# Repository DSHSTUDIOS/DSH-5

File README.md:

# DSH-5

I wanted a DJ deck I could hold in one hand. The DSH-5 has a motorized platter for scratching, a small OLED, one crossfader and one level knob. REC, MIX and PLAY are on the right edge. The seesaw on the left speeds up or slows down the track.

## Playing it

1. Put a stereo, 16-bit, 44.1 kHz `BACKING.WAV` on a microSD card. The deck loops the first 30 seconds. Add a `SCRATCH.WAV` for a separate sample. The wheel uses the backing track if there is no sample or recording.
2. Hold **PLAY** to turn it on. Tap **PLAY** to start or pause. Press either end of the seesaw to change the backing track speed.
3. Tap **MIX** to scratch. The motor lets the platter coast, and turning it moves the scratch sample. Use the crossfader to blend it with the backing track. The knob sets the output level.
4. Tap **REC** to capture up to eight seconds from line in. Tap it again to save the take and use it as the scratch sample.

## Design screenshots

### Enclosure and board

### Rev E PCB

## Rev E prototype

Rev E uses a solder-down ESP32-S3, a bare OLED, and an onboard stereo codec. The main board carries the crossfader, level pot, three side buttons and the two speed-seesaw contacts.

| What | Where |
| --- | --- |
| PCB | [KiCad project](hardware/rev-e/kicad/DSH-5-PCB-RevE.kicad_pro) · [board](hardware/rev-e/kicad/DSH-5-PCB-RevE.kicad_pcb) · [schematic](hardware/rev-e/kicad/DSH-5-PCB-RevE.kicad_sch) |
| Parts and sourcing | [Full BOM](BOM.csv) · [Fallen BOM](FALLEN-BOM.csv) |
| Mechanical reference | [Populated PCB STEP](cad/DSH-5-RevE-PCB.step.xz) |
| Wiring and assembly | [Hardware and turnkey assembly notes](hardware/rev-e/README.md) · [KiCad and firmware reports](hardware/rev-e/checks/) |
| Firmware | [ESP32-S3 source](firmware/rev-e/src/) · [PlatformIO project](platformio.ini) |

Run `pio run` from the repository root to build Rev E. Unpack the PCB model with `xz -dk cad/DSH-5-RevE-PCB.step.xz` and open the resulting STEP in Fusion.

KiCad reports zero errors and zero open connections, with two warnings documented in the hardware notes. The firmware builds. Physical fit, charging, audio and the motor still need first-article testing.

## Rev D files

The studio render and enclosure images above show Rev D. Its [enclosure and fit notes](cad/README.md), [KiCad source](hardware/kicad/DSH-5-PCB-RevD.kicad_pro), [turnkey quote files](hardware/manufacturing/pcba/), and [Teensy firmware](firmware/README.md) are available for that revision. The [Rev D BOM](https://github.com/DSHSTUDIOS/DSH-5/blob/5f626b1eb498d4edce1bb6fbd1a963682ae008fc/BOM.csv) is in the prior release commit.

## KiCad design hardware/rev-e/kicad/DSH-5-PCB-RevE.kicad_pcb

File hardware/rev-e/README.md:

# DSH-5 Rev E

Rev E puts the microcontroller, audio codec, display support, microSD and 3.3 V supply on the DSH-5 main board. The four-layer, 80 × 176 mm board carries the 30 mm crossfader, level potentiometer, three side switches and two switches for the opposite-side seesaw.

## Hardware

| Reference | Implementation |
| --- | --- |
| U1 | Solder-down ESP32-S3-WROOM-1-N16R8 with 16 MB flash and 8 MB PSRAM. |
| DS1 and J20 | Bare 0.96-inch Winstar OLED with 30-pin FPC and 0.5 mm ZIF connector. The main PCB provides the SSD1306 charge-pump capacitors and current reference. The I²C address is 0x3C. |
| J6 and U2 | JST-XH alternate line input. The main PCB provides ESD protection, 1 kΩ series protection, 100 kΩ bias returns and 2.2 µF AC coupling into the TLV320AIC3204 codec. J11 is the alternative 3.5 mm input. Connect one source at a time. |
| J12 and J13 | Separate 3.5 mm line and headphone outputs from the onboard codec. |
| J21 | Direct-mounted microSD socket on SPI with its own chip select. |
| U14 and U3 | Onboard MCP2518FD CAN-FD controller and TCAN3413 PHY. This preserves the interface to the motor controller. |
| J1 and J2 | USB-C PD charging and internal protected 3S battery. The USB-C connector supplies power. J19 provides the firmware service interface. |

The GL30 motor, moteus-c1 controller and Pololu 12 V regulator remain chassis-mounted. The full BOM includes them. The Fallen CSV excludes the two ready-made chassis boards from the funding request. Every row has a USD price and a sourcing link. Listed prices and estimates are identified in the full BOM. The OLED price is a per-deck budget figure based on an 11-piece supplier minimum. The custom battery and harnesses have budget figures pending quotes. The full budget is $602.63 and the Fallen budget is $503.68, including a $250.00 CNC enclosure allowance. These subtotals precede supplier order minimums, PCB and harness assembly labor, tax and shipping.

## Files

- `kicad/DSH-5-PCB-RevE.kicad_pro` opens the editable schematic and PCB. KiCad 10 standard footprint and 3D model libraries supplement the local project libraries.
- [DSH-5-RevE-PCB.step.xz](../../cad/DSH-5-RevE-PCB.step.xz) contains the populated PCB reference for Fusion. Run `xz -dk cad/DSH-5-RevE-PCB.step.xz` from the repository root to extract it. Its origin is the board's upper-left corner. The OLED panel and motor mount separately in the enclosure. Fit a nonconductive fastener at H2 and keep metal out of the antenna area. Recheck the OLED flex fold, microSD access, service header and headphone cutout with physical samples.
- [BOM.csv](../../BOM.csv) lists components and sourcing links. [FALLEN-BOM.csv](../../FALLEN-BOM.csv) uses the proposal's CSV columns.
- Build the [ESP32-S3 firmware](../../firmware/rev-e/src/) with `pio run` from the repository root. The PlatformIO board manifest configures the compiler and flash settings.

## Verification

The schematic passed KiCad electrical checks. The PCB passed routing and schematic parity checks with zero errors and no unconnected items. KiCad flags the customized ESP32 antenna footprint because its placement rule allows the nearby unplated H2 mounting hole. The area still excludes pads, tracks, vias and copper pours. KiCad also reports an unterminated copper branch with continuity intact. The ESP32-S3 firmware compiled. Physical OLED fit, USB-C charging, audio and motor behavior still need first-article validation.

## CNC enclosure

Budget one CNC-machined chassis, front plate and rear cover. The allowance assumes 6061 aluminum with a standard machined finish. The enclosure STEP in the repository is from Rev D. Check the Rev E OLED, microSD, headphones, service access and antenna clearance in the enclosure before quoting the final case.

The battery tray budget is 65 × 37 × 20 mm. The pack vendor needs to confirm the complete wrapped dimensions, wire exit and connector fit as well as cell balancing, 12.6 V charge termination, 1 A charge and at least 3 A continuous discharge. The BT1 link is for sourcing a custom configuration. [PCBWay CNC quote](https://www.pcbway.com/rapid-prototyping/)

## Turnkey assembly

Quote both-sided SMT, through-hole controls and connectors, and factory programming. Specify that the assembled board should arrive with all soldering finished. If the order includes the whole deck, quote installing the OLED into J20, mounting the controls and motor stack, and building the keyed chassis harnesses as separate integration operations.

J19 pin order is GND, ESP TX, ESP RX, BOOT, EN, and 3.3 V reference. Use a 3.3 V UART fixture. For download mode, hold BOOT low while cycling EN low then high. Use `pio run -t upload` through the fixture after the board is powered. The USB-C connector is for charging.

[Winstar OLED panel options](https://www.winstar.com.tw/products/oled-module/graphic-oled-display/0_96-oled.html) · [ESP32-S3 module datasheet](https://documentation.espressif.com/esp32-s3-wroom-1_wroom-1u_datasheet_en.pdf) · [TI audio codec](https://www.ti.com/product/TLV320AIC3204) · [PCBWay turnkey assembly quote](https://www.pcbway.com/quotesmt.aspx)

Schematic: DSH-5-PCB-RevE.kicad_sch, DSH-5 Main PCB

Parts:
C1: 470u / 35V; CP_Radial_D10.0mm_P5.00mm
C2, C24, C25, C26, C42, C55: 100n / 50V; C_0603_1608Metric
C3, C4, C5, C6: 100n; C_0805_2012Metric
C10, C11: 330p; C_0603_1608Metric
C12: 1n; C_0603_1608Metric
C13, C14, C51, C61, C74, C75, C94: 10u / 10V; C_0805_2012Metric
C15, C22: 4.7u / 10V; C_0805_2012Metric
C16: 4.7u / 35V; C_0805_2012Metric
C17: 10n / 50V; C_0603_1608Metric
C18, C19: 22u / 35V; C_1206_3216Metric
C20, C21: 47n / 25V; C_0603_1608Metric
C23: 1n / 50V; C_0402_1005Metric
C27, C28, C29, C30, C31, C32, C33, C34, C35, C36, C37, C38, C53: 10u / 35V; C_1206_3216Metric
C43, C46, C52, C58, C59, C60, C85, C92, C95: 100n; C_0603_1608Metric
C44: 330n; C_0603_1608Metric
C50, C56, C57, C62, C84, C93: 1u / 10V; C_0805_2012Metric
C54: 22u / 10V; C_1206_3216Metric
C70, C71: 2.2u / 10V; C_0805_2012Metric
C76, C77: 47u / 10V; C_1206_3216Metric
C80, C81: 1u / 16V; C_0805_2012Metric
C82, C83: 1u / 25V; C_0805_2012Metric
C90, C91: 15p C0G; C_0603_1608Metric
D1, D10: SMBJ16A; D_SMB
D4: SS54; D_SMC
D5: BZT52C10; D_SOD-123
D6, D7, D8, D9, D11, D12: PESD5V0S1BA; D_SOD-323
F1: 2 A / 32 V; Fuse_1206_3216Metric
F2: 3 A / 32 V; Fuse_1206_3216Metric
J1: USB-C CHARGE; USB_C_Receptacle_GCT_USB4125-xx-x_6P_TopMnt_Horizontal
J2: BATTERY; Battery_VH_2Pin_Edge
J3: PACK TEMP; JST_PH_B2B-PH-K_1x02_P2.00mm_Vertical
J4: BRAKE RESISTOR; JST_VH_B2P-VH_1x02_P3.96mm_Vertical
J6: AUX STEREO LINE IN; JST_XH_B3B-XH-A_1x03_P2.50mm_Vertical
J7: STEREO LINE OUT HEADER; JST_XH_B3B-XH-A_1x03_P2.50mm_Vertical
J8: CHARGER DEBUG; JST_XH_B3B-XH-A_1x03_P2.50mm_Vertical
J11: STEREO LINE IN; Line_Jack_SJ3523SMT
J12: STEREO LINE OUT; Line_Jack_SJ3523SMT
J13: HEADPHONES; Line_Jack_SJ3523SMT
J17: MOTEUS CAN; JST_PH_B3B-PH-K_1x03_P2.00mm_Vertical
J18: MOTEUS POWER; JST_VH_B2P-VH_1x02_P3.96mm_Vertical
J19: 3V3 UART SERVICE; PinHeader_1x06_P2.54mm_Vertical
J20: OLED FPC; Hirose_FH12-30S-0.5SH_1x30-1MP_P0.50mm_Horizontal
J21: MICROSD SPI; microSD_HC_Hirose_DM3AT-SF-PEJM5
L1: 2.2uH; L_Coilcraft_XAL6060-XXX
L2: 2.2uH; L_Wuerth_MAPI-3012
Q1: IRLML6344; SOT-23
Q2: DMP3010LK3; TO-252-3_TabPin2
Q3: 2N7002; SOT-23
R1: 120R; R_0805_2012Metric
R3, R4: 1k; R_0805_2012Metric
R5: 10k; R_0805_2012Metric
R10: 82.5k 1%; R_0603_1608Metric
R11, R13, R31: 10k 1%; R_0603_1608Metric
R12: 200k 1%; R_0603_1608Metric
R14: 69.8k 1%; R_0603_1608Metric
R15, R23: 30.1k 1%; R_0603_1608Metric
R16, R21, R47: 100k 1%; R_0603_1608Metric
R17: 13k 1%; R_0603_1608Metric
R18: 0R; R_0603_1608Metric
R19: 13.7k 1%; R_0603_1608Metric
R20: 162k 1%; R_0603_1608Metric
R22: 5.23k 1%; R_0603_1608Metric
R24, R42, R43, R44, R45: 100R; R_0603_1608Metric
R25, R26, R27, R40, R41, R50, R51, R55, R70, R71, R72, R73, R74, R75, R76: 10k; R_0603_1608Metric
R30: 49.9k 1%; R_0603_1608Metric
R32: 1M 1%; R_0603_1608Metric
R33, R34: 2.2k; R_0603_1608Metric
R46, R58, R59, R62, R63: 100k; R_0603_1608Metric
R48: 24.9k 1%; R_0603_1608Metric
R53, R54: 4.7k; R_0603_1608Metric
R56, R57: 1k; R_0603_1608Metric
R60, R61: 47k; R_0603_1608Metric
R66: 910k; R_0603_1608Metric
RV1: B10k fader; Potentiometer_Bourns_PTA3043_Single_Slide
RV2: B10k knob; Potentiometer_Bourns_PTV09A-1_Single_Vertical
SW1: REC; SW_Tactile_SPST_Angled_PTS645Vx39-2LFS
SW2: MIX; SW_Tactile_SPST_Angled_PTS645Vx39-2LFS
SW3: PLAY / POWER; SW_Tactile_SPST_Angled_PTS645Vx39-2LFS
SW4: SPEED +; SW_Tactile_SPST_Angled_PTS645Vx39-2LFS
SW5: SPEED -; SW_Tactile_SPST_Angled_PTS645Vx39-2LFS
U1: ESP32-S3-WROOM-1-N16R8; ESP32-S3-WROOM-1
U2: TLV320AIC3204; Texas_RHB0032E_VQFN-32-1EP_5x5mm_P0.5mm_EP3.45x3.45mm
U3: TCAN3413DR; SOIC-8_3.9x4.9mm_P1.27mm
U4: TPS62162; Texas_DSG0008A_WSON-8-1EP_2x2mm_P0.5mm_EP0.9x1.6mm
U6: MOTOR REGULATOR HARNESS; JST_VH_B4P-VH_1x04_P3.96mm_Vertical
U7: TPS25730D; Texas_REF0038A_WQFN-38-2EP_6x4mm_P0.4
U8: TPS22810; SOT-23-6
U9: BQ25798; Texas_RQM0029A_VQFN-29_4x4mm_P0.4mm
U10: LTC2954-1; TSOT-23-8
U11: TLV1701; SOT-23-5
U12: TL431A; SOT-23
U13: TLV75518; SOT-23-5
U14: MCP2518FD; SOIC-14_3.9x8.7mm_P1.27mm
Y1: 40MHz; Crystal_SMD_3225-4Pin_3.2x2.5mm

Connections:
/+3V3: C3.1, C4.1, C51.1, C52.1, C54.1, C56.1, C58.1, C62.1, C84.1, C85.1, C92.1, C93.1, C94.1, C95.1, J19.6 (VREF), J20.6 (VBAT), J20.9 (VDD), J20.11 (BS1), J21.4 (VDD), L2.2 (3V3), Q3.1 (GATE), R5.1, R25.1, R26.1, R27.1, R40.1, R41.1, R50.1, R51.1, R53.1, R54.1, R70.1, R71.1, R72.1, R73.1, R74.1, R75.1, R76.1, RV1.3 (Low), RV2.3 (Low), U1.2 (3V3), U2.6 (IOVDD), U2.26 (LDOIN), U3.3 (VCC), U3.5 (VIO), U4.6 (VOS), U13.1 (IN), U13.3 (EN), U14.14 (VDD)
/AUX_IN_L: D11.1 (K), J6.1 (L), R56.1
/AUX_IN_R: D12.1 (K), J6.3 (R), R57.1
/BAT_FUSED: C27.1, C28.1, F2.2, Q2.3 (SOURCE), R24.1, R46.1, U9.22 (BAT), U9.23 (BAT)
/BRAKE_GATE: D5.1 (K), Q1.1 (GATE), R32.1, R33.2, U11.4 (OUT)
/BRAKE_REF: R34.2, U11.3 (IN-), U12.1 (REF), U12.2 (CATHODE)
/BRAKE_RETURN: J4.2 (RETURN), Q1.3 (DRAIN)
/BRAKE_SENSE: R30.2, R31.1, R32.2, U11.1 (IN+)
/BST1: C20.1, U9.4 (BTST1)
/BST2: C21.1, U9.19 (BTST2)
/CAN_CS_N: R70.2, U1.34 (IO41), U14.13 (CS#)
/CAN_H: J17.1 (CAN_H), R1.1, U3.7 (CANH)
/CAN_IRQ_N: R71.2, U1.11 (IO18), U14.4 (INT)
/CAN_L: J17.2 (CAN_L), R1.2, U3.6 (CANL)
/CAN_RX: U3.4 (RXD), U14.2 (RXCAN)
/CAN_TX: R5.2, U3.1 (TXD), U14.1 (TXCAN)
/CAN_XI: C90.1, U14.6 (OSC1), Y1.1 (XI)
/CAN_XO: C91.1, U14.5 (OSC2), Y1.3 (XO)
/CHG_DM: R18.2, U9.7 (D-)
/CHG_DP: R18.1, U9.6 (D+)
/CHG_ILIM: R20.2, R21.1, U9.17 (ILIM_HIZ)
/CHG_N: R25.2, U1.24 (IO47), U9.1 (STAT)
/CHG_PMID: C25.1, C31.1, C32.1, C33.1, U9.29 (PMID)
/CHG_PROG: R19.1, U9.20 (PROG)
/CHG_REGN: C22.1, R20.1, R22.1, U9.5 (REGN)
/CHG_SCL: J8.2 (SCL), R26.2, U9.14 (SCL)
/CHG_SDA: J8.1 (SDA), R27.2, U9.15 (SDA)
/CHG_SDRV: C23.1, U9.24 (SDRV)
/CHG_SENSE: R24.2, U9.18 (BATP)
/CHG_SW1: C20.2, L1.1 (SW1), U9.28 (SW1)
/CHG_SW2: C21.2, L1.2 (SW2), U9.26 (SW2)
/CHG_VIN: C24.1, C29.1, C30.1, U8.6 (VOUT), U9.2 (VBUS), U9.3 (VBUS), U9.8 (VAC2), U9.9 (VAC1)
/CODEC_1V8: C57.1, C59.1, C60.1, U2.24 (AVDD), U2.29 (DVDD), U13.5 (OUT)
/CODEC_HPL: C76.1, U2.25 (HPL)
/CODEC_HPR: C77.1, U2.27 (HPR)
/CODEC_IN_L: C70.2, U2.13 (IN1_L)
/CODEC_IN_R: C71.2, U2.14 (IN1_R)
/CODEC_LOL: C74.1, U2.22 (LOL)
/CODEC_LOR: C75.1, U2.23 (LOR)
/CODEC_REF: C61.1, U2.18 (REF)
/CODEC_RESET: R55.1, U1.23 (IO21), U2.31 (RESET)
/GND: C1.2 (-), C2.2, C3.2, C4.2, C5.2, C6.2, C10.2, C11.2, C12.2, C13.2, C14.2, C15.2, C16.2, C17.2, C18.2, C19.2, C22.2, C23.2, C24.2, C25.2, C26.2, C27.2, C28.2, C29.2, C30.2, C31.2, C32.2, C33.2, C34.2, C35.2, C36.2, C37.2, C38.2, C42.2, C43.2, C44.2, C46.2, C50.2, C51.2, C52.2, C53.2, C54.2, C55.2, C56.2, C57.2, C58.2, C59.2, C60.2, C61.2, C62.2, C82.2, C83.2, C84.2, C85.2, C90.2, C91.2, C92.2, C93.2, C94.2, C95.2, D1.2 (A), D5.2 (A), D6.2 (A), D7.2 (A), D8.2 (A), D9.2 (A), D10.2 (A), D11.2 (A), D12.2 (A), J1.A12 (GND), J1.B12 (GND), J1.SH (SHELL), J2.2 (PACK_-), J3.2 (GND), J6.2 (GND), J7.2 (GND), J8.3 (GND), J11.S (GND), J12.S (GND), J13.S (GND), J17.3 (GND), J18.2 (GND), J19.1 (GND), J20.1 (NC_GND), J20.8 (VSS), J20.10 (BS0), J20.12 (BS2), J20.13 (CS#), J20.15 (SA0), J20.16 (R/W#), J20.17 (E/RD#), J20.21 (D3), J20.22 (D4), J20.23 (D5), J20.24 (D6), J20.25 (D7), J20.29 (VLSS), J20.30 (NC_GND), J21.6 (VSS), J21.SH (SHIELD), Q1.2 (SOURCE), Q3.2 (SOURCE), R11.2, R13.2, R15.2, R17.2, R19.2, R21.2, R23.2, R31.2, R48.2, R55.2, R58.2, R59.2, R60.2, R61.2, R62.2, R63.2, R66.2, RV1.1 (High), RV2.1 (High), SW1.2 (COM), SW2.2 (COM), SW3.2 (COM), SW4.2 (COM), SW5.2 (COM), U1.1 (GND), U1.40 (GND), U1.41 (EPAD), U2.7 (IOVSS), U2.8 (SCLK), U2.12 (SPI_SELECT), U2.17 (AVSS), U2.28 (DVSS), U2.30 (LDO_SELECT), U2.33 (EP), U3.2 (GND), U3.8 (STB), U4.1 (PGND), U4.4 (AGND), U4.5 (FB), U4.9 (EP), U6.3 (GND), U7.8 (I2C_SDA), U7.9 (I2C_SCL), U7.11 (PGND), U7.12 (PGND), U7.14 (PGND), U7.16 (PGND), U7.17 (PGND), U7.26 (RESERVED), U7.27 (RESERVED), U7.31 (PGND), U7.34 (PGND), U7.36 (RESERVED), U7.39 (PGND), U8.2 (GND), U9.10 (ACDRV2), U9.11 (ACDRV1), U9.13 (CE), U9.27 (GND), U10.4 (GND), U11.2 (V-), U12.3 (ANODE), U13.2 (GND), U14.7 (VSS), Y1.2 (CASE), Y1.4 (CASE)
/HP_L: C76.2, J13.T (L), R62.1
/HP_R: C77.2, J13.R, R63.1
/I2C_SCL: J20.18 (D0_SCL), R53.2, U1.19 (IO11), U2.9 (SCL)
/I2C_SDA: J20.19 (D1_SDA), J20.20 (D2_SDA), R54.2, U1.18 (IO10), U2.10 (SDA)
/I2S_ADC: U1.9 (IO16), U2.5 (DOUT)
/I2S_BCLK: U1.21 (IO13), U2.2 (BCLK)
/I2S_DAC: U1.8 (IO15), U2.4 (DIN)
/I2S_LRCLK: U1.22 (IO14), U2.3 (WCLK)
/I2S_MCLK: U1.20 (IO12), U2.1 (MCLK)
/KILL_OK: R41.2, U10.8 (KILL)
/LEVEL_ADC: C6.1, R4.2, U1.38 (IO2)
/LINE_IN_L: C70.1, R42.2, R56.2, R58.1
/LINE_IN_L_EXT: D6.1 (K), J11.T (LEFT), R42.1
/LINE_IN_R: C71.1, R43.2, R57.2, R59.1
/LINE_IN_R_EXT: D7.1 (K), J11.R (RIGHT), R43.1
/LINE_OUT_L: C74.2, J7.1 (L), R44.2, R60.1
/LINE_OUT_L_EXT: D8.1 (K), J12.T (LEFT), R44.1
/LINE_OUT_R: C75.2, J7.3 (R), R45.2, R61.1
/LINE_OUT_R_EXT: D9.1 (K), J12.R (RIGHT), R45.1
/LOGIC_SW: L2.1 (SW), U4.7 (SW)
/MCU_BOOT_N: J19.4 (BOOT), R51.2, U1.27 (IO0)
/MCU_EN: C50.1, J19.5 (EN), R50.2, U1.3 (EN)
/MIX_N: SW2.1 (NO), U1.6 (IO6)
/MOTOR_FUSED: D4.2 (A), F1.2
/MOTOR_RAW: F1.1, U6.4 (VOUT)
/OLED_C1N: C80.2, J20.5 (C1N)
/OLED_C1P: C80.1, J20.4 (C1P)
/OLED_C2N: C81.2, J20.2 (C2N)
/OLED_C2P: C81.1, J20.3 (C2P)
/OLED_COM: C83.1, J20.27 (VCOMH)
/OLED_IREF: J20.26 (IREF), R66.1
/OLED_PANEL_VCC: C82.1, J20.28 (VCC)
/OLED_RESET: J20.14 (RES#), U1.10 (IO17)
/PACK_RAW: F2.1, J2.1 (PACK_+)
/PACK_TS: J3.1 (NTC), R22.2, R23.1, U9.16 (TS)
/PD_1V5: C15.1, U7.3 (ADCIN2), U7.4 (LDO_1V5)
/PD_3V3: C14.1, R10.1, R12.1, R14.1, U7.1 (LDO_3V3), U7.18 (FAULT_IN)
/PD_DRAIN: U7.15 (DRAIN), U7.30 (DRAIN), U7.40 (DRAIN_PAD)
/PD_IMAX: R14.2, R15.1, U7.7 (ADCIN4)
/PD_IOP: R12.2, R13.1, U7.5 (ADCIN3)
/PD_MIN: R10.2, R11.1, U7.2 (ADCIN1)
/PD_SLEW: C12.1, U8.4 (CT)
/PD_VIN_3V3: C13.1, U7.38 (VIN_3V3)
/PD_VOUT: C18.1, C19.1, R16.1, U7.20 (PPHV), U8.1 (VIN)
/PD_VQUAL: R16.2, R17.1, U8.3 (EN)
/PLAY_N: R40.2, U1.7 (IO7), U10.5 (INT)
/POWER_BUTTON_N: SW3.1 (NO), U10.2 (PB)
/POWER_EN: U4.3 (EN), U6.1 (EN), U10.6 (EN)
/REC_N: SW1.1 (NO), U1.5 (IO5)
/SD_CS_N: J21.2 (DAT3_CS), R72.2, U1.35 (IO42)
/SD_DAT1: J21.8 (DAT1), R73.2
/SD_DAT2: J21.1 (DAT2), R74.2
/SENSE_GATE: Q2.1 (GATE), Q3.3 (DRAIN), R46.2
/SENSE_SRC: Q2.2 (DRAIN), R47.1
/SPEED_DN_N: SW5.1 (NO), U1.17 (IO9)
/SPEED_UP_N: SW4.1 (NO), U1.12 (IO8)
/SPI_MISO: J21.7 (DAT0), R76.2, U1.33 (IO40), U14.12 (SDO)
/SPI_MOSI: J21.3 (CMD), R75.2, U1.32 (IO39), U14.11 (SDI)
/SPI_SCK: J21.5 (CLK), U1.31 (IO38), U14.10 (SCK)
/SW_ONT: C43.1, U10.3 (ONT)
/SW_PDT: C44.1, U10.7 (PDT)
/SYS_BAT: C26.1, C34.1, C35.1, C36.1, C37.1, C38.1, C53.1, C55.1, U4.2 (VIN), U6.2 (VIN), U9.25 (SYS), U10.1 (VIN)
/UART_RX: J19.3 (ESP_RX), U1.36 (RXD0)
/UART_TX: J19.2 (ESP_TX), U1.37 (TXD0)
/USB_CC1: C10.1, J1.A5 (CC1), U7.28 (CC1)
/USB_CC2: C11.1, J1.B5 (CC2), U7.29 (CC2)
/USB_VBUS: C16.1, C17.1, D10.1 (K), J1.A9 (VBUS), J1.B9 (VBUS), U7.23 (VBUS_IN), U7.32 (LDO_VBUS)
/VBAT_ADC: C46.1, R47.2, R48.1, U1.4 (IO4)
/VM_12V: C1.1 (+), C2.1, C42.1, D1.1 (K), D4.1 (K), J4.1 (VM), J18.1 (VM_+), R30.1, R33.1, R34.1, U11.5 (V+)
/XFADER_ADC: C5.1, R3.2, U1.39 (IO1)
unnamed: R3.1, RV1.2 (Wiper)
unnamed: R4.1, RV2.2 (Wiper)

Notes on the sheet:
Verify pin-1 orientation, exposed contact side and fold in a physical sample.
ONBOARD STEREO CODEC / INPUT AND OUTPUT
RAW SSD1306 OLED / 30-PIN FPC
USB-C POWER DELIVERY / INPUT QUALIFICATION
BQ25798 POWER PATH / PROTECTED 3S BATTERY
FRONT CONTROLS / DIRECT PCB MOUNT
Set codec inputs and common-mode in firmware before enabling audio.
DS1: Winstar WEO012864DWPP3N00F04 bare OLED.
SSD1306 I2C address 0x3C. Use internal charge pump.
The 3.3 V buck powers the logic and raises KILL_OK.
J6 or J11 is the stereo source. Use one at a time.
OLED uses J20 and on-board charge pump passives.
SUPPLY / POWER BUTTON / MONITORING
Place CC filters and raw VBUS decoupling at the PD controller. Do not ground PD_DRAIN.
RV1 is the crossfader. RV2 sets output level.
MOTOR RAIL / REVERSE ISOLATION / REGENERATIVE SHUNT
Use the specified external pulse resistor. Start with conservative moteus current and regen limits.
SCRATCH MOTOR / MOTEUS-C1
J17 is carrier order H/L/GND; match the moteus connector by SIGNAL.
Keep copper and metal away from the antenna area.
Connect a protected, balanced 3S pack rated for 1 A charge and 3 A continuous discharge.
BOARD-MOUNT STEREO AUDIO / BATTERY SENSE
Control power stays off until PLAY is held. Brief presses drive the ESP32.
SW1-SW3 mount at the right edge. SW4 and SW5 sit under one left-edge rocker.
GPIO35–37 are reserved by octal PSRAM. Flash through J19.
The rocker returns to center. SW3 goes to the power controller. ESP32 reads the controller INT output.
Autonomous charge configuration: 3S, 12.60 V, 1.00 A, 750 kHz. Charge can run while the deck is off.
Shunt turns on near 15 V and off near 14.5 V.
Input bleed and ESD are on board. AC couple into internally biased PGA.
DSH-5 / PCB REV E
ESP32-S3 / CONTROLS / SERVICE
GL30 motor phases U/V/W wire directly to moteus, outside this PCB.
CAN-FD CONTROLLER / MICROSD
Current limited to about 1.15 A at the charger input. Requires a 12 V or 15 V USB-PD source.
Fit a second 120R terminator at the far controller end.
FOUR-LAYER MAIN BOARD | FRONT WHEEL + FADER + KNOB | SIDE REC / MIX / PLAY
See assembly STEP for the GL30 platter stack and magnetic encoder gap.
The local D+/D- strap selects DCP limits after the PD switch. The analog input ceiling is lower.
ONBOARD 3.3 V LOGIC SUPPLY
Separate SPI chip selects. Configure 1 Mbps arbitration and 5 Mbps data, verify against motor setup.

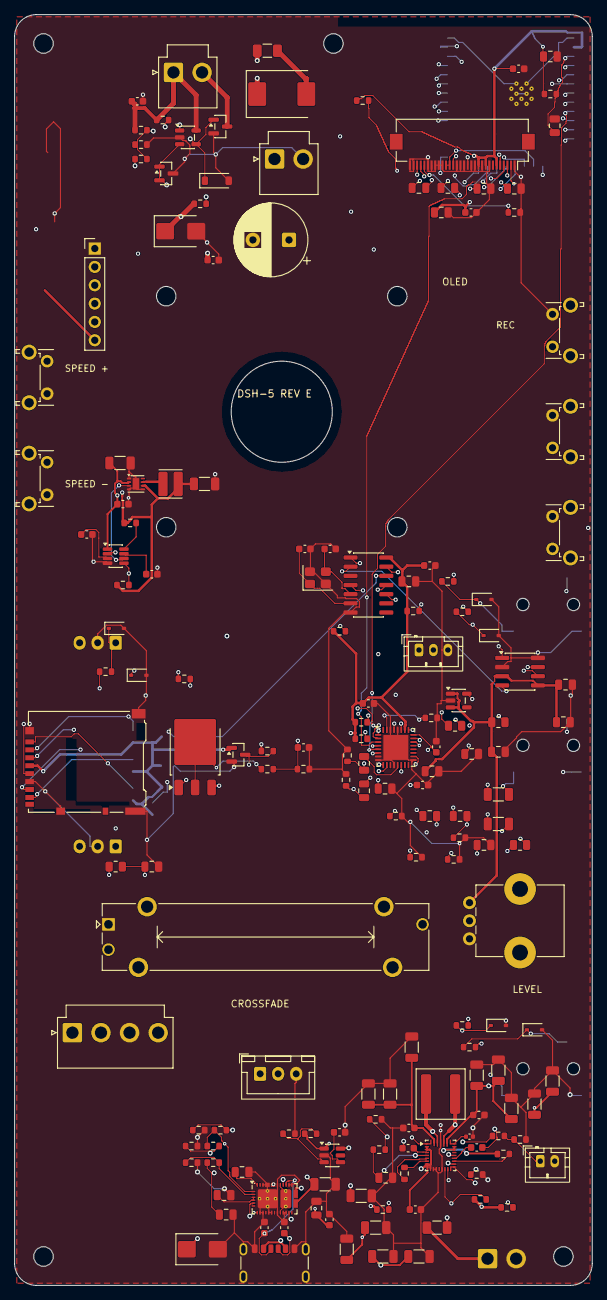
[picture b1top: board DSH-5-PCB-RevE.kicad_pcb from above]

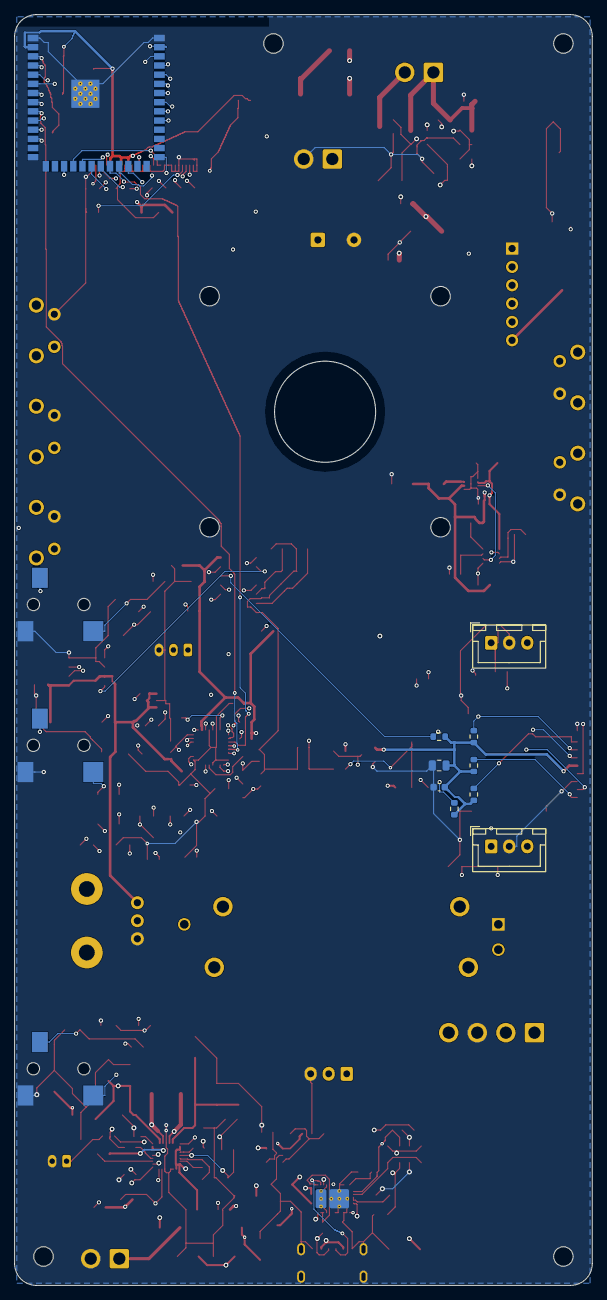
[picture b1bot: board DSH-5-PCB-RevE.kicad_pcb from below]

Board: 4 copper layers, 80.0 x 176.0 mm, 188 parts (13 on the bottom side), 114 nets.

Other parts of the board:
H1, H2, H3, H4, H5, H6, H7, H8: M2.5; MountingHole_2.7mm_M2.5

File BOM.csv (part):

Designator,Quantity,Part or value,Footprint,Assembly role,Assembly scope,Quote part or specification,Unit price USD,Extended price USD,Price type,Price source,Price checked,Procurement notes
C1,1,Panasonic EEU-FR1V471,Capacitor_THT:CP_Radial_D10.0mm_P5.00mm,,Main PCB,Panasonic EEU-FR1V471,1.08,1.08,Listed,https://www.digikey.com/en/products/detail/panasonic-industr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,2026-11-22,Polarity and body clearance.
C10,1,330p,Capacitor_SMD:C_0603_1608Metric,,Main PCB,330 pF 50 V C0G ±5%,0.12,0.12,Estimate,https://www.digikey.com/en/products/result?keywords=330+pF+5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,2026-11-22,Assembler may source to the listed requirements.
C11,1,330p,Capacitor_SMD:C_0603_1608Metric,,Main PCB,330 pF 50 V C0G ±5%,0.12,0.12,Estimate,https://www.digikey.com/en/products/result?keywords=330+pF+5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,2026-11-22,Assembler may source to the listed requirements.
C12,1,1n,Capacitor_SMD:C_0603_1608Metric,,Main PCB,1 nF 50 V C0G ±5%,0.14,0.14,Estimate,https://www.digikey.com/en/products/result?keywords=1+nF+50+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,2026-11-22,Assembler may source to the listed requirements.
C13,1,10u / 10V,Capacitor_SMD:C_0805_2012Metric,,Main PCB,10 µF ≥10 V X5R/X7R ±20%,0.24,0.24,Estimate,https://www.digikey.com/en/products/result?keywords=10+%C2%B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,2026-11-22,Assembler may source to the listed requirements.
C14,1,10u / 10V,Capacitor_SMD:C_0805_2012Metric,,Main PCB,10 µF ≥10 V X5R/X7R ±20%,0.24,0.24,Estimate,https://www.digikey.com/en/products/result?keywords=10+%C2%B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,2026-11-22,Assembler may source to the listed requirements.
C15,1,4.7u / 10V,Capacitor_SMD:C_0805_2012Metric,,Main PCB,4.7 µF ≥10 V X5R/X7R ±20%,0.20,0.20,Estimate,https://www.digikey.com/en/products/result?keywords=4.7+%C2%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,2026-11-22,Assembler may source to the listed requirements.
C16,1,4.7u / 35V,Capacitor_SMD:C_0805_2012Metric,,Main PCB,4.7 µF ≥35 V X5R/X7R ±20%,0.33,0.33,Estimate,https://www.digikey.com/en/products/result?keywords=4.7+%C2%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,2026-11-22,Assembler may source to the listed requirements.
C17,1,10n / 50V,Capacitor_SMD:C_0603_1608Metric,,Main PCB,10 nF ≥50 V X7R ±10%,0.10,0.10,Estimate,https://www.digikey.com/en/products/result?keywords=10+nF+%E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,2026-11-22,Assembler may source to the listed requirements.
C18,1,22u / 35V,Capacitor_SMD:C_1206_3216Metric,,Main PCB,22 µF ≥35 V X5R/X7R ±20%,0.89,0.89,Estimate,https://www.digikey.com/en/products/result?keywords=22+%C2%B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,2026-11-22,Check effective capacitance at operating voltage for charger bulk capacitors.
C19,1,22u / 35V,Capacitor_SMD:C_1206_3216Metric,,Main PCB,22 µF ≥35 V X5R/X7R ±20%,0.89,0.89,Estimate,https://www.digikey.com/en/products/result?keywords=22+%C2%B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,2026-11-22,Check effective capacitance at operating voltage for charger bulk capacitors.
C2,1,100n / 50V,Capacitor_SMD:C_0603_1608Metric,,Main PCB,100 nF ≥50 V X7R ±10%,0.13,0.13,Estimate,https://www.digikey.com/en/products/result?keywords=100+nF+%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,2026-11-22,Assembler may source to the listed requirements.
C20,1,47n / 25V,Capacitor_SMD:C_0603_1608Metric,,Main PCB,47 nF ≥25 V X7R ±10%,0.12,0.12,Estimate,https://www.digikey.com/en/products/result?keywords=47+nF+%E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,2026-11-22,Assembler may source to the listed requirements.
C21,1,47n / 25V,Capacitor_SMD:C_0603_1608Metric,,Main PCB,47 nF ≥25 V X7R ±10%,0.12,0.12,Estimate,https://www.digikey.com/en/products/result?keywords=47+nF+%E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,2026-11-22,Assembler may source to the listed requirements.
C22,1,4.7u / 10V,Capacitor_SMD:C_0805_2012Metric,,Main PCB,4.7 µF ≥10 V X5R/X7R ±20%,0.20,0.20,Estimate,https://www.digikey.com/en/products/result?keywords=4.7+%C2%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,2026-11-22,Assembler may source to the listed requirements.
C23,1,1n / 50V,Capacitor_SMD:C_0402_1005Metric,,Main PCB,1 nF ≥50 V C0G/X7R ±10%,0.15,0.15,Estimate,https://www.digikey.com/en/products/result?keywords=1+nF+%E2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,2026-11-22,Assembler may source to the listed requirements.
C24,1,100n / 50V,Capacitor_SMD:C_0603_1608Metric,,Main PCB,100 nF ≥50 V X7R ±10%,0.13,0.13,Estimate,https://www.digikey.com/en/products/result?keywords=100+nF+%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,2026-11-22,Assembler may source to the listed requirements.
C25,1,100n / 50V,Capacitor_SMD:C_0603_1608Metric,,Main PCB,100 nF ≥50 V X7R ±10%,0.13,0.13,Estimate,https://www.digikey.com/en/products/result?keywords=100+nF+%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,2026-11-22,Assembler may source to the listed requirements.
C26,1,100n / 50V,Capacitor_SMD:C_0603_1608Metric,,Main PCB,100 nF ≥50 V X7R ±10%,0.13,0.13,Estimate,https://www.digikey.com/en/products/result?keywords=100+nF+%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,2026-11-22,Assembler may source to the listed requirements.
C27,1,10u / 35V,Capacitor_SMD:C_1206_3216Metric,,Main PCB,10 µF ≥35 V X5R/X7R ±20%,0.55,0.55,Estimate,https://www.digikey.com/en/products/result?keywords=10+%C2%B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,2026-11-22,Check effective capacitance at operating voltage for charger bulk capacitors.
C28,1,10u / 35V,Capacitor_SMD:C_1206_3216Metric,,Main PCB,10 µF ≥35 V X5R/X7R ±20%,0.55,0.55,Estimate,https://www.digikey.com/en/products/result?keywords=10+%C2%B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,2026-11-22,Check effective capacitance at operating voltage for charger bulk capacitors.
C29,1,10u / 35V,Capacitor_SMD:C_1206_3216Metric,,Main PCB,10 µF ≥35 V X5R/X7R ±20%,0.55,0.55,Estimate,https://www.digikey.com/en/products/result?keywords=10+%C2%B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,2026-11-22,Check effective capacitance at operating voltage for charger bulk capacitors.
C3,1,100 nF X7R 50 V 0805,Capacitor_SMD:C_0805_2012Metric,Decoupling or ADC filter,Main PCB,100 nF ≥50 V X7R ±10%,0.15,0.15,Estimate,https://www.digikey.com/en/products/result?keywords=100+nF+%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,2026-11-22,Assembler may source to the listed requirements.
C30,1,10u / 35V,Capacitor_SMD:C_1206_3216Metric,,Main PCB,10 µF ≥35 V X5R/X7R ±20%,0.55,0.55,Estimate,https://www.digikey.com/en/products/result?keywords=10+%C2%B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,2026-11-22,Check effective capacitance at operating voltage for charger bulk capacitors.
C31,1,10u / 35V,Capacitor_SMD:C_1206_3216Metric,,Main PCB,10 µF ≥35 V X5R/X7R ±20%,0.55,0.55,Estimate,https://www.digikey.com/en/products/result?keywords=10+%C2%B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,2026-11-22,Check effective capacitance at operating voltage for charger bulk capacitors.
C32,1,10u / 35V,Capacitor_SMD:C_1206_3216Metric,,Main PCB,10 µF ≥35 V X5R/X7R ±20%,0.55,0.55,Estimate,https://www.digikey.com/en/products/result?keywords=10+%C2%B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,2026-11-22,Check effective capacitance at operating voltage for charger bulk capacitors.
C33,1,10u / 35V,Capacitor_SMD:C_1206_3216Metric,,Main PCB,10 µF ≥35 V X5R/X7R ±20%,0.55,0.55,Estimate,https://www.digikey.com/en/products/result?keywords=10+%C2%B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,2026-11-22,Check effective capacitance at operating voltage for charger bulk capacitors.
C34,1,10u / 35V,Capacitor_SMD:C_1206_3216Metric,,Main PCB,10 µF ≥35 V X5R/X7R ±20%,0.55,0.55,Estimate,https://www.digikey.com/en/products/result?keywords=10+%C2%B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,2026-11-22,Check effective capacitance at operating voltage for charger bulk capacitors.
C35,1,10u / 35V,Capacitor_SMD:C_1206_3216Metric,,Main PCB,10 µF ≥35 V X5R/X7R ±20%,0.55,0.55,Estimate,https://www.digikey.com/en/products/result?keywords=10+%C2%B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,2026-11-22,Check effective capacitance at operating voltage for charger bulk capacitors.
C36,1,10u / 35V,Capacitor_SMD:C_1206_3216Metric,,Main PCB,10 µF ≥35 V X5R/X7R ±20%,0.55,0.55,Estimate,https://www.digikey.com/en/products/result?keywords=10+%C2%B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,2026-11-22,Check effective capacitance at operating voltage for charger bulk capacitors.
C37,1,10u / 35V,Capacitor_SMD:C_1206_3216Metric,,Main PCB,10 µF ≥35 V X5R/X7R ±20%,0.55,0.55,Estimate,https://www.digikey.com/en/products/result?keywords=10+%C2%B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,2026-11-22,Check effective capacitance at operating voltage for charger bulk capacitors.
C38,1,10u / 35V,Capacitor_SMD:C_1206_3216Metric,,Main PCB,10 µF ≥35 V X5R/X7R ±20%,0.55,0.55,Estimate,https://www.digikey.com/en/products/result?keywords=10+%C2%B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,2026-11-22,Check effective capacitance at operating voltage for charger bulk capacitors.
C4,1,100 nF X7R 50 V 0805,Capacitor_SMD:C_0805_2012Metric,Decoupling or ADC filter,Main PCB,100 nF ≥50 V X7R ±10%,0.15,0.15,Estimate,https://www.digikey.com/en/products/result?keywords=100+nF+%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,2026-11-22,Assembler may source to the listed requirements.
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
